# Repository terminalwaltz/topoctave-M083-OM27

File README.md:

# topoctave-M083-OM27

Building on this amazing work to adapt for Omnichord OM-27's M083 tone generator.

----

Creating a Top Octave Organ Tone Generator using PIOs on the Pi Pico in micropython

Use Thonny to upload main.py and ws2812.py to the RP2040. Hardware designed in Eagle, Gerbers provided.

Blog post here:  https://www.cctv.fm/post/rp2040-tog

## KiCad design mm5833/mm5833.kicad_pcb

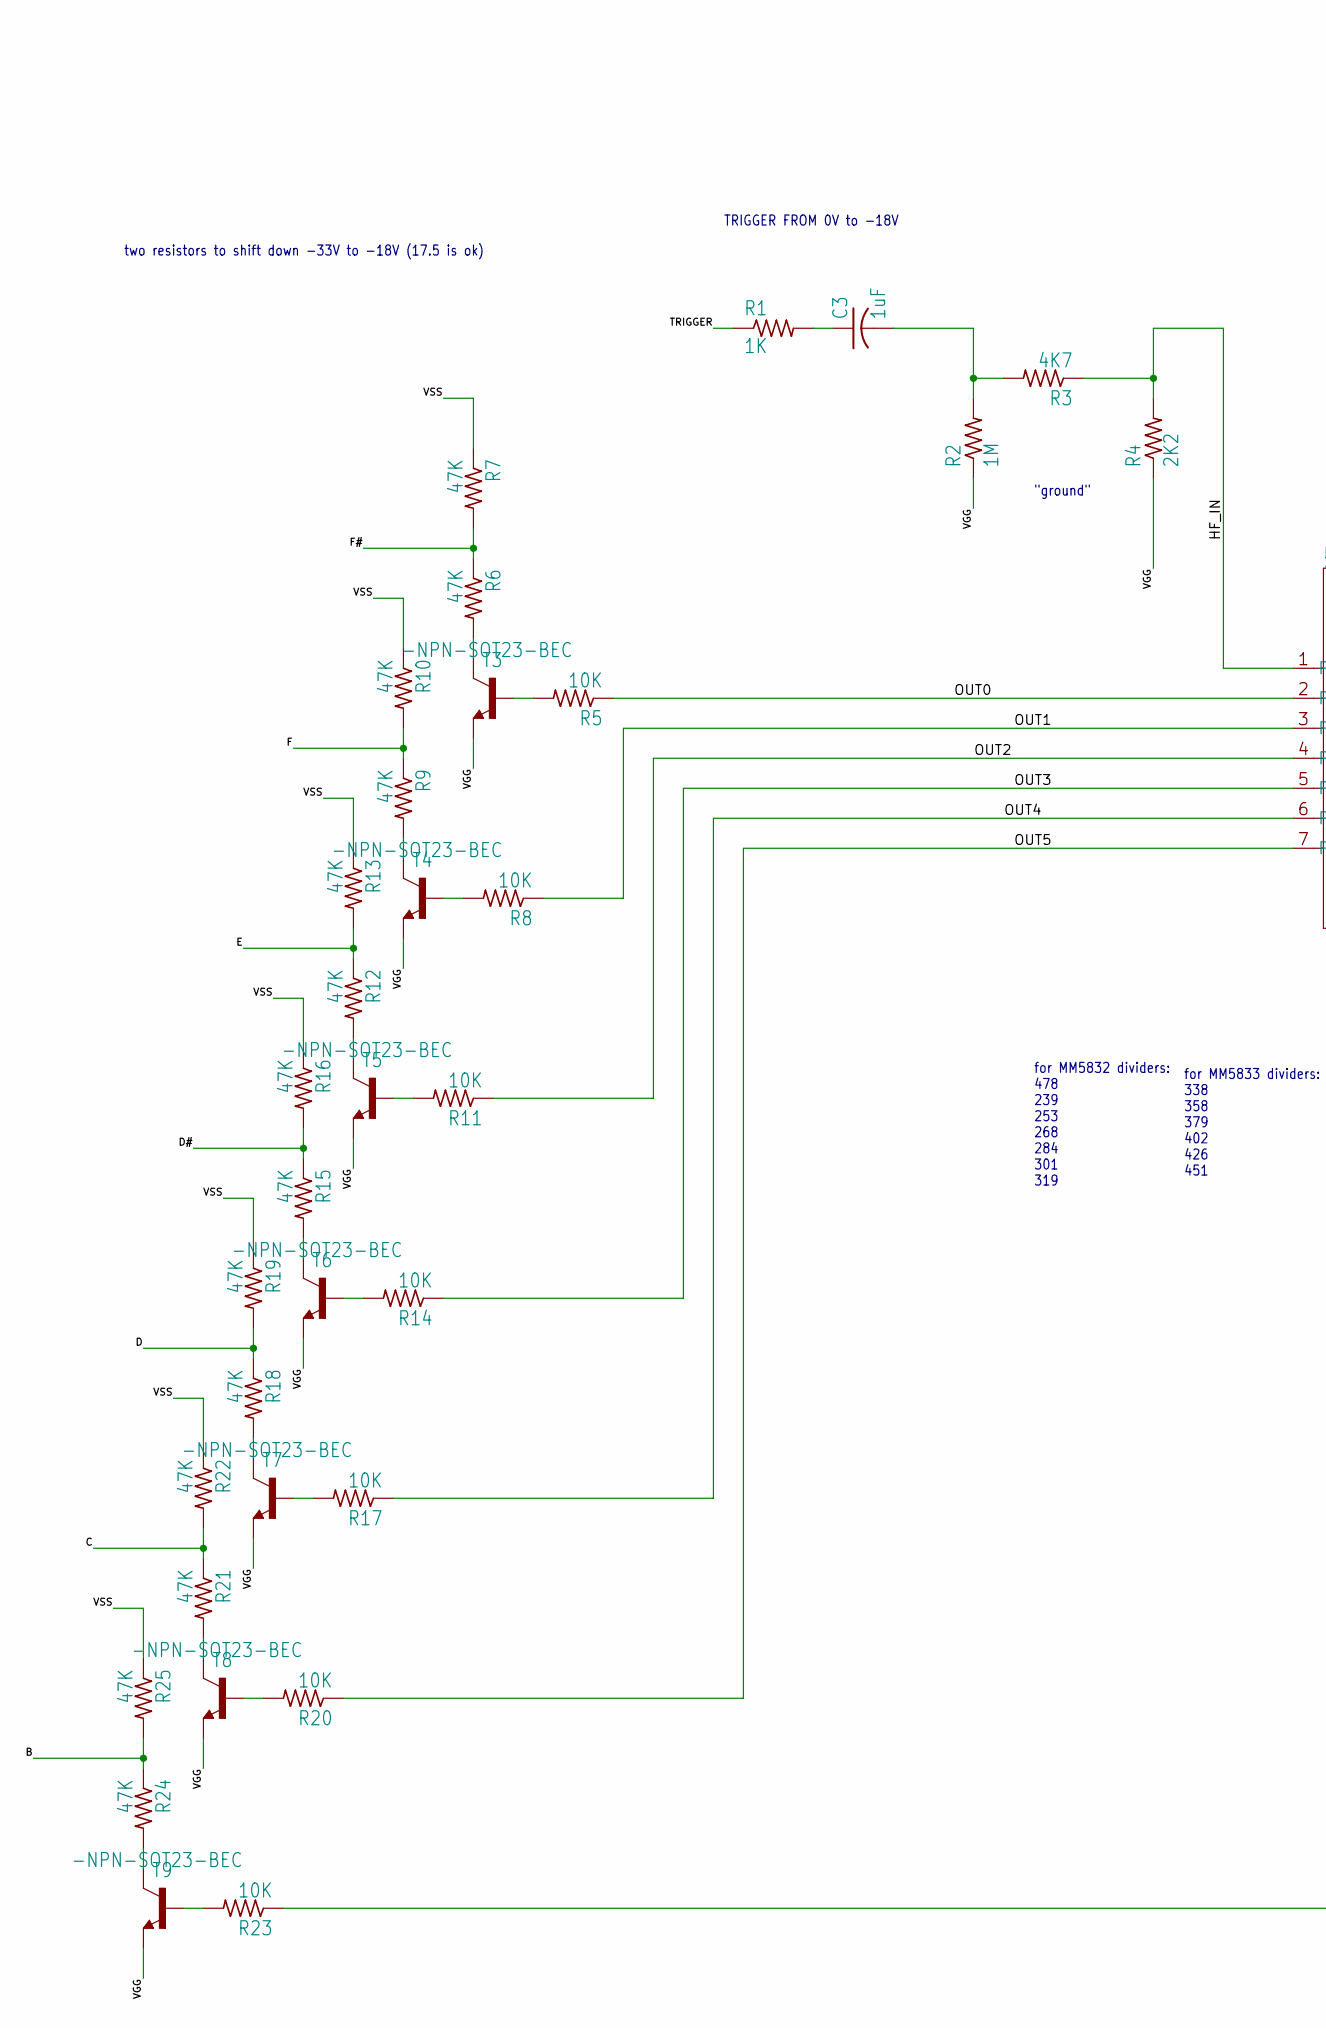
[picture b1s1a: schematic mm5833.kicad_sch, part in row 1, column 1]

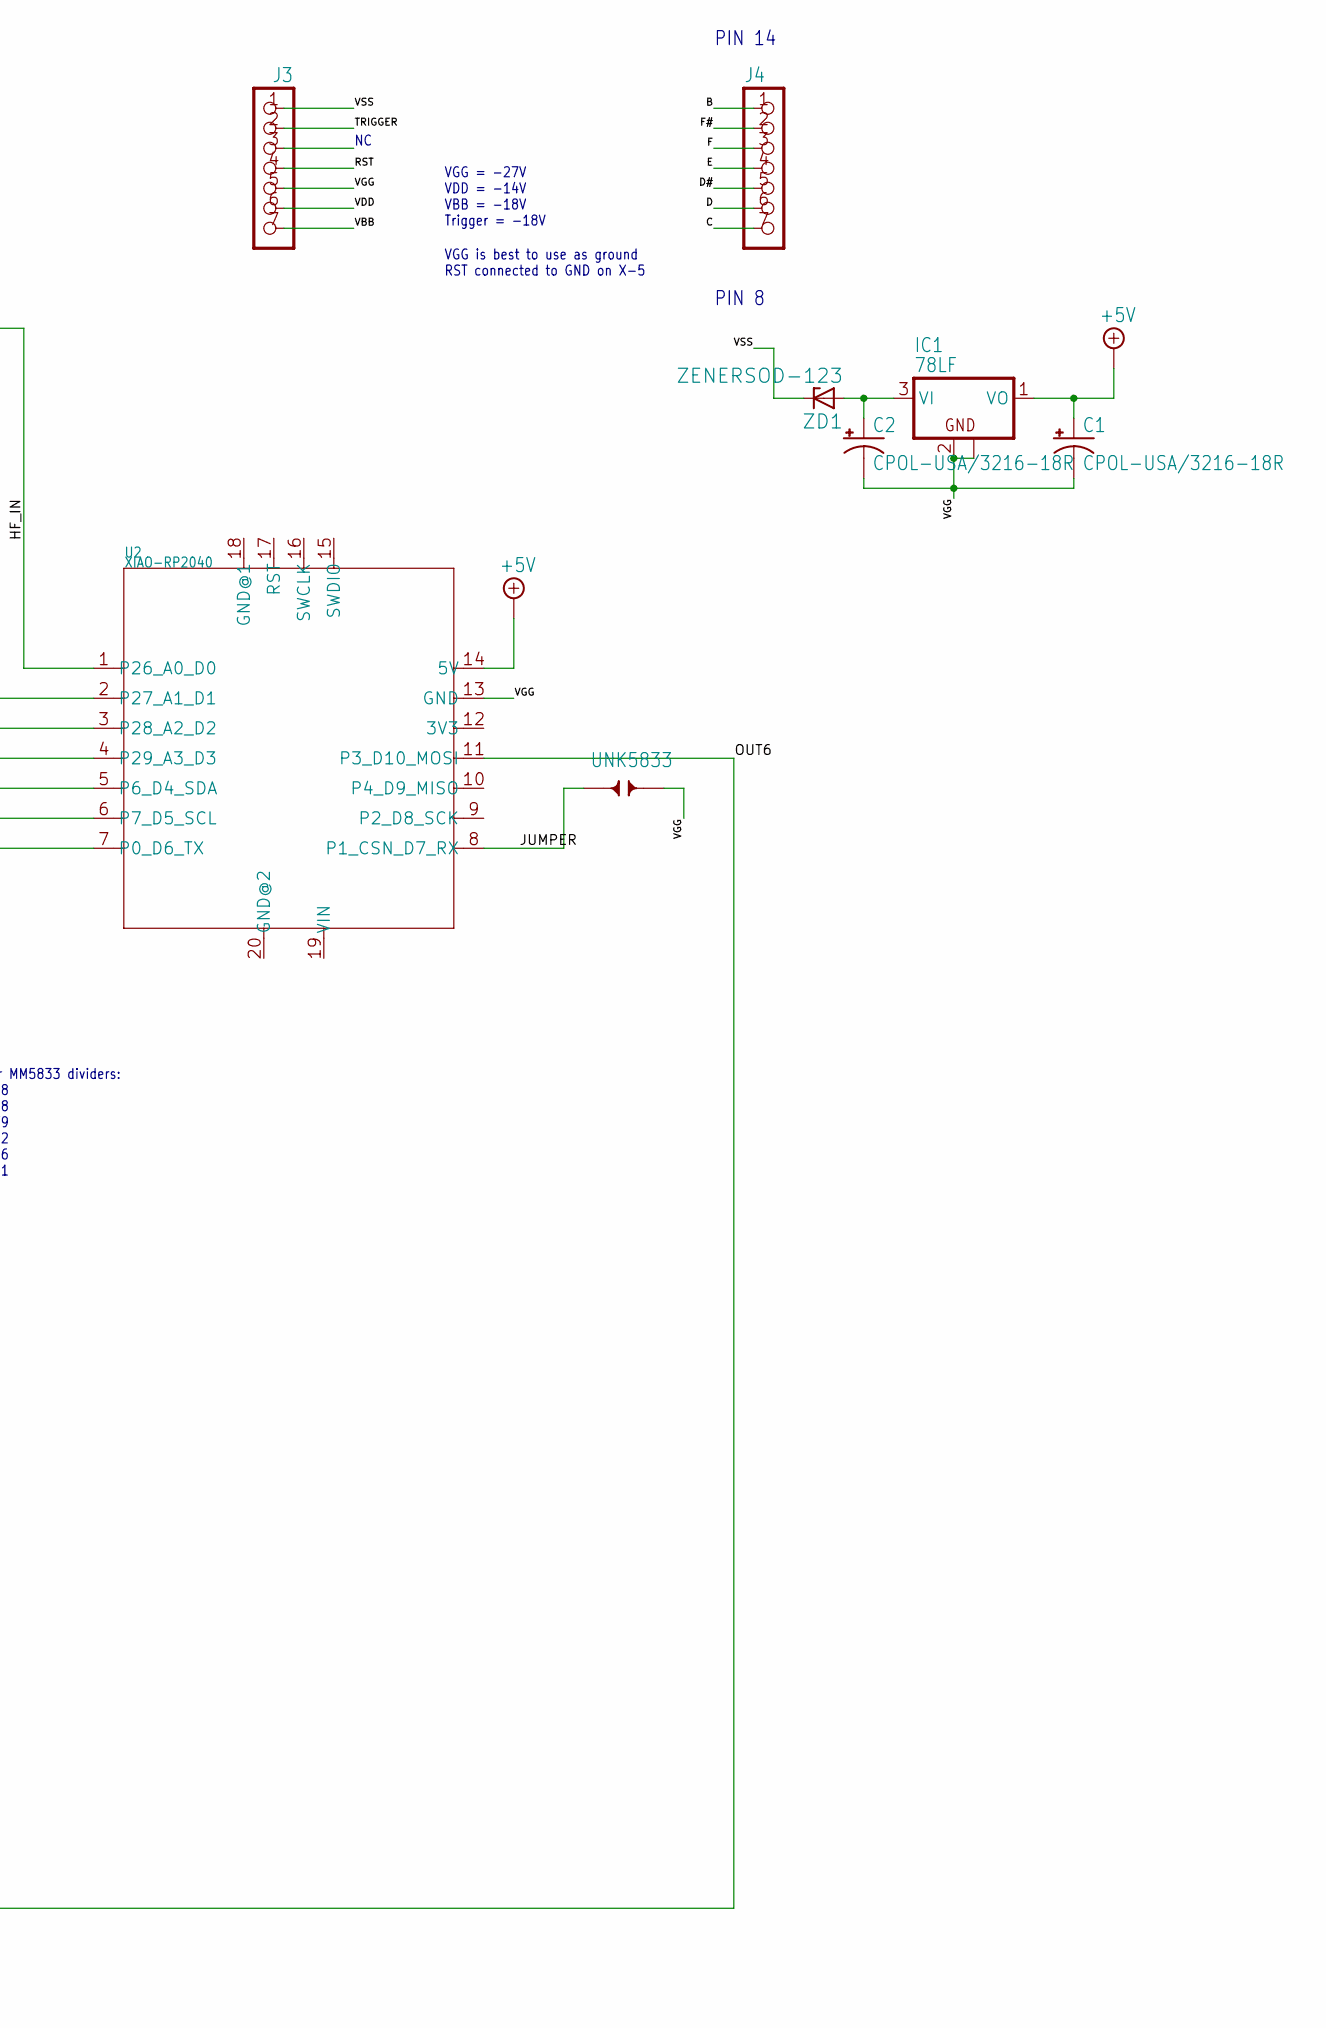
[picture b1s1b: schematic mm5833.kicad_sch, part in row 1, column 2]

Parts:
C1, C2: CPOL-USA/3216-18R; A_3216-18R
C3: 1uF; C0805
IC1: 78LF; SOT89
J3, J4: CON_HEADER_1X07; M1X7_SMD
R1: 1K; R0603
R2: 1M; R0603
R3: 4K7; R0603
R4: 2K2; R0603
R5, R8, R11, R14, R17, R20, R23: 10K; R0603
R6, R7, R9, R10, R12, R13, R15, R16, R18, R19, R21, R22, R24, R25: 47K; R0603
T3, T4, T5, T6, T7, T8, T9: -NPN-SOT23-BEC; SOT23-BEC
U2: XIAO-RP2040; XIAO-SAMD21_RP2040-MODULE14P-2.54-21X17.8MM
UNK5833: JUMPER_SOLDER_1X2
ZD1: ZENERSOD-123; SOD-123

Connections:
+5V: C1.+, IC1.1 (VO), U2.14 (5V)
B: J4.1, R24.1, R25.2
C: J4.7, R21.1, R22.2
D: J4.6, R18.1, R19.2
D#: J4.5, R15.1, R16.2
E: J4.4, R12.1, R13.2
F: J4.3, R9.1, R10.2
F#: J4.2, R6.1, R7.2
HF_IN: R3.1, R4.2, U2.1 (P26_A0_D0)
JUMPER: U2.8 (P1_CSN_D7_RX), UNK5833.1
unnamed: C2.+, IC1.3 (VI), ZD1.A
unnamed: C3.1, R1.2
unnamed: C3.2, R2.2, R3.2
unnamed: R5.2, T3.B
unnamed: R6.2, T3.C
unnamed: R8.2, T4.B
unnamed: R24.2, T9.C
unnamed: R9.2, T4.C
unnamed: R11.2, T5.B
unnamed: R12.2, T5.C
unnamed: R14.2, T6.B
unnamed: R23.2, T9.B
unnamed: R15.2, T6.C
unnamed: R17.2, T7.B
unnamed: R18.2, T7.C
unnamed: R20.2, T8.B
unnamed: R21.2, T8.C
OUT0: R5.1, U2.2 (P27_A1_D1)
OUT1: R8.1, U2.3 (P28_A2_D2)
OUT2: R11.1, U2.4 (P29_A3_D3)
OUT3: R14.1, U2.5 (P6_D4_SDA)
OUT4: R17.1, U2.6 (P7_D5_SCL)
OUT5: R20.1, U2.7 (P0_D6_TX)
OUT6: R23.1, U2.11 (P3_D10_MOSI)
RST: J3.4
TRIGGER: J3.2, R1.1
VBB: J3.7
VDD: J3.6
VGG: C1.-, C2.-, IC1.2 (GND), IC1.2@1 (GND@1), J3.5, R2.1, R4.1, T3.E, T4.E, T5.E, T6.E, T7.E, T8.E, T9.E, U2.13 (GND), UNK5833.2
VSS: J3.1, R7.1, R10.1, R13.1, R16.1, R19.1, R22.1, R25.1, ZD1.C

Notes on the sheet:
TRIGGER FROM 0V to -18V
for MM5833 dividers: 338 358 379 402 426 451
for MM5832 dividers: 478 239 253 268 284 301 319
PIN 8
VGG = -27V VDD = -14V VBB = -18V Trigger = -18V
two resistors to shift down -33V to -18V (17.5 is ok)
"ground"
PIN 14
VGG is best to use as ground RST connected to GND on X-5

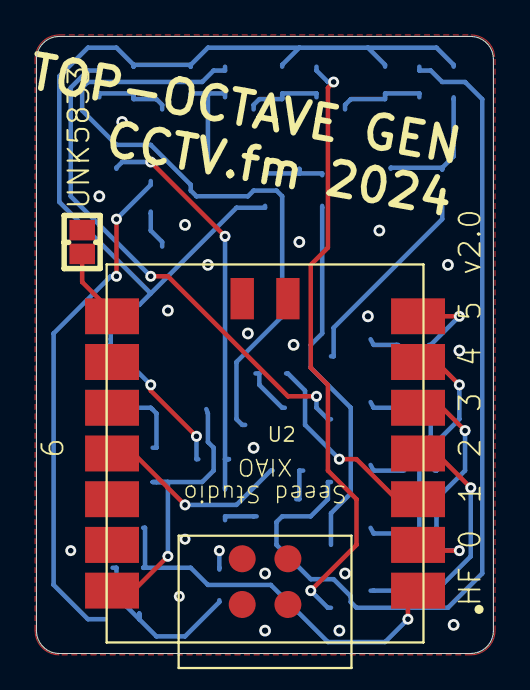
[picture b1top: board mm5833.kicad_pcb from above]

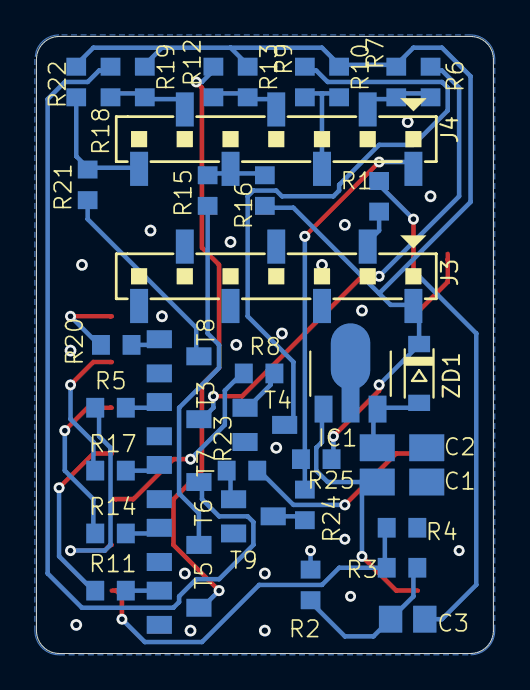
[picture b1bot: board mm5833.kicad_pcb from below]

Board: 2 copper layers, 25.4 x 34.3 mm, 41 parts (39 on the bottom side), 37 nets.

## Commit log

2026-04-15 Rename project and enhance README description
    Updated project name and added description for OM-27 adaptation.
2026-04-15 EAGLE to KiCAD import
